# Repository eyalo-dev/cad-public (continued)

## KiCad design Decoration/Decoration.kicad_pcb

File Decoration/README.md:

Name:
- Decoration

Description:
- Decoration/fun, ball shap (christmas ornament), blinking LEDs.

Source refrence:
- Elektor Electronics 1003-12 p.104

This is functional similar but not exact copy.
All dimensions were estimated by eye.
Tried to use similar component placment as much as posible, but using only Kicad
standard PCB component footprint library, so dimentions may very.

PCB
- Done edit but
- Not tested

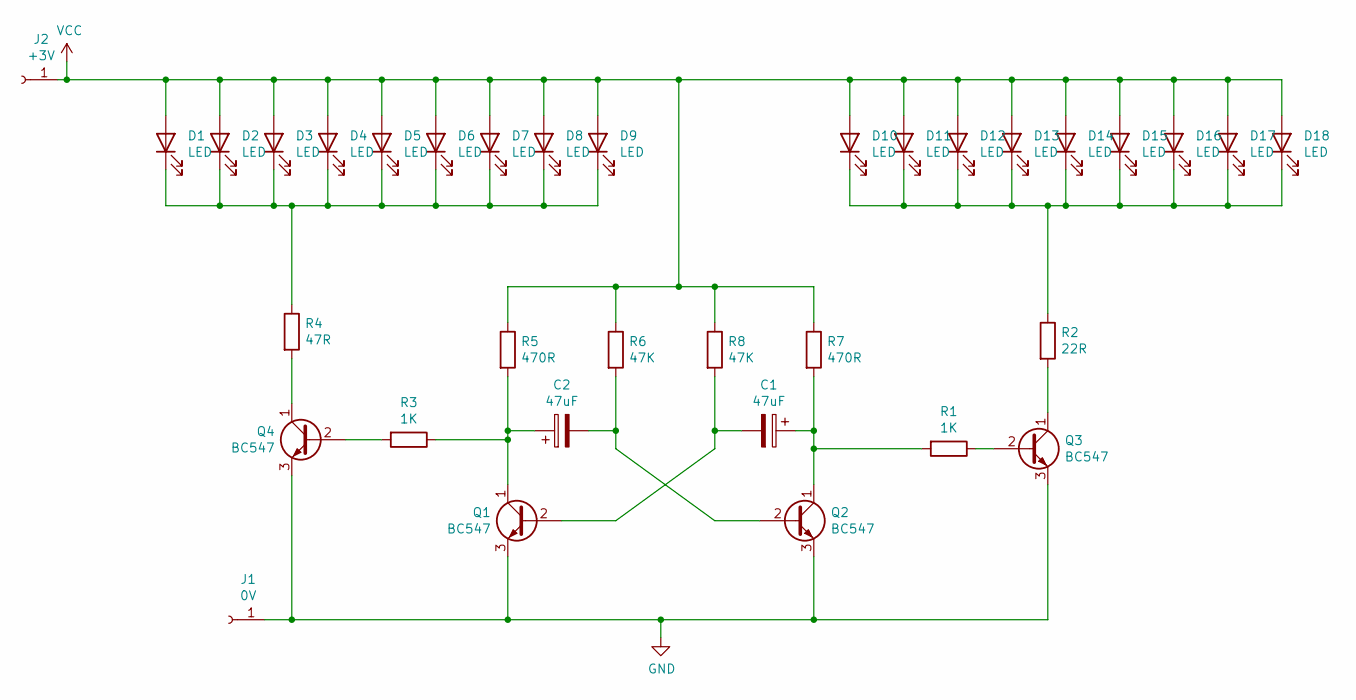
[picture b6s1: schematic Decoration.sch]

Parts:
C1, C2: 47uF; CP_Radial_Tantal_D7.0mm_P5.00mm
D1, D2, D3, D4, D5, D6, D7, D8, D9, D10, D11, D12, D13, D14, D15, D16, D17, D18: LED; LED_D5.0mm_Clear
J1: 0V; PinHeader_1x01_P2.54mm_Vertical
J2: +3V; PinHeader_1x01_P2.54mm_Vertical
Q1, Q2, Q3, Q4: BC547; TO-92_Inline
R1, R3: 1K; R_Axial_DIN0207_L6.3mm_D2.5mm_P10.16mm_Horizontal
R2: 22R; R_Axial_DIN0207_L6.3mm_D2.5mm_P10.16mm_Horizontal
R4: 47R; R_Axial_DIN0207_L6.3mm_D2.5mm_P10.16mm_Horizontal
R5, R7: 470R; R_Axial_DIN0207_L6.3mm_D2.5mm_P10.16mm_Horizontal
R6, R8: 47K; R_Axial_DIN0207_L6.3mm_D2.5mm_P10.16mm_Horizontal

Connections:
GND: J1.1, Q1.3 (E), Q2.3 (E), Q3.3 (E), Q4.3 (E)
unnamed: C1.1, Q2.1 (C), R1.2, R7.2
unnamed: C1.2, Q1.2 (B), R8.2
unnamed: C2.1, Q1.1 (C), R3.1, R5.2
unnamed: C2.2, Q2.2 (B), R6.2
unnamed: D1.1 (K), D2.1 (K), D3.1 (K), D4.1 (K), D5.1 (K), D6.1 (K), D7.1 (K), D8.1 (K), D9.1 (K), R4.1
unnamed: D10.1 (K), D11.1 (K), D12.1 (K), D13.1 (K), D14.1 (K), D15.1 (K), D16.1 (K), D17.1 (K), D18.1 (K), R2.1
unnamed: Q3.1 (C), R2.2
unnamed: Q3.2 (B), R1.1
unnamed: Q4.1 (C), R4.2
unnamed: Q4.2 (B), R3.2
VCC: D1.2 (A), D2.2 (A), D3.2 (A), D4.2 (A), D5.2 (A), D6.2 (A), D7.2 (A), D8.2 (A), D9.2 (A), D10.2 (A), D11.2 (A), D12.2 (A), D13.2 (A), D14.2 (A), D15.2 (A), D16.2 (A), D17.2 (A), D18.2 (A), J2.1, R5.1, R6.1, R7.1, R8.1

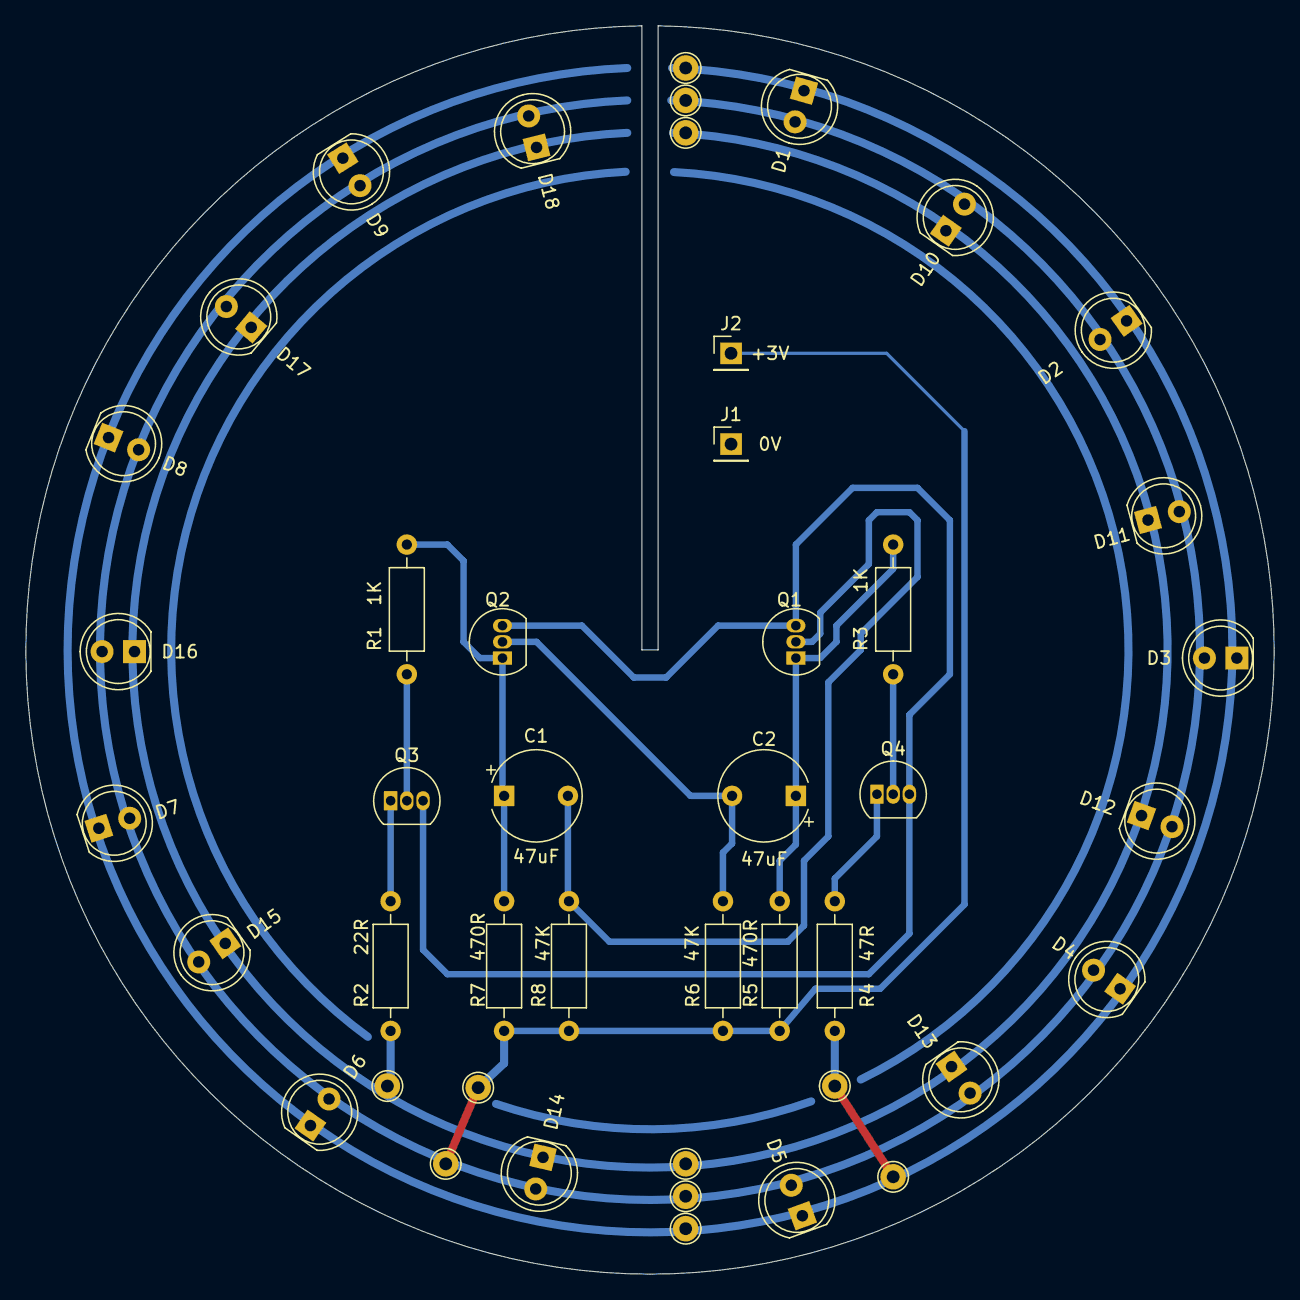
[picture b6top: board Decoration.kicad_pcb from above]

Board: 2 copper layers, 97.8 x 97.8 mm, 34 parts (0 on the bottom side), 12 nets.

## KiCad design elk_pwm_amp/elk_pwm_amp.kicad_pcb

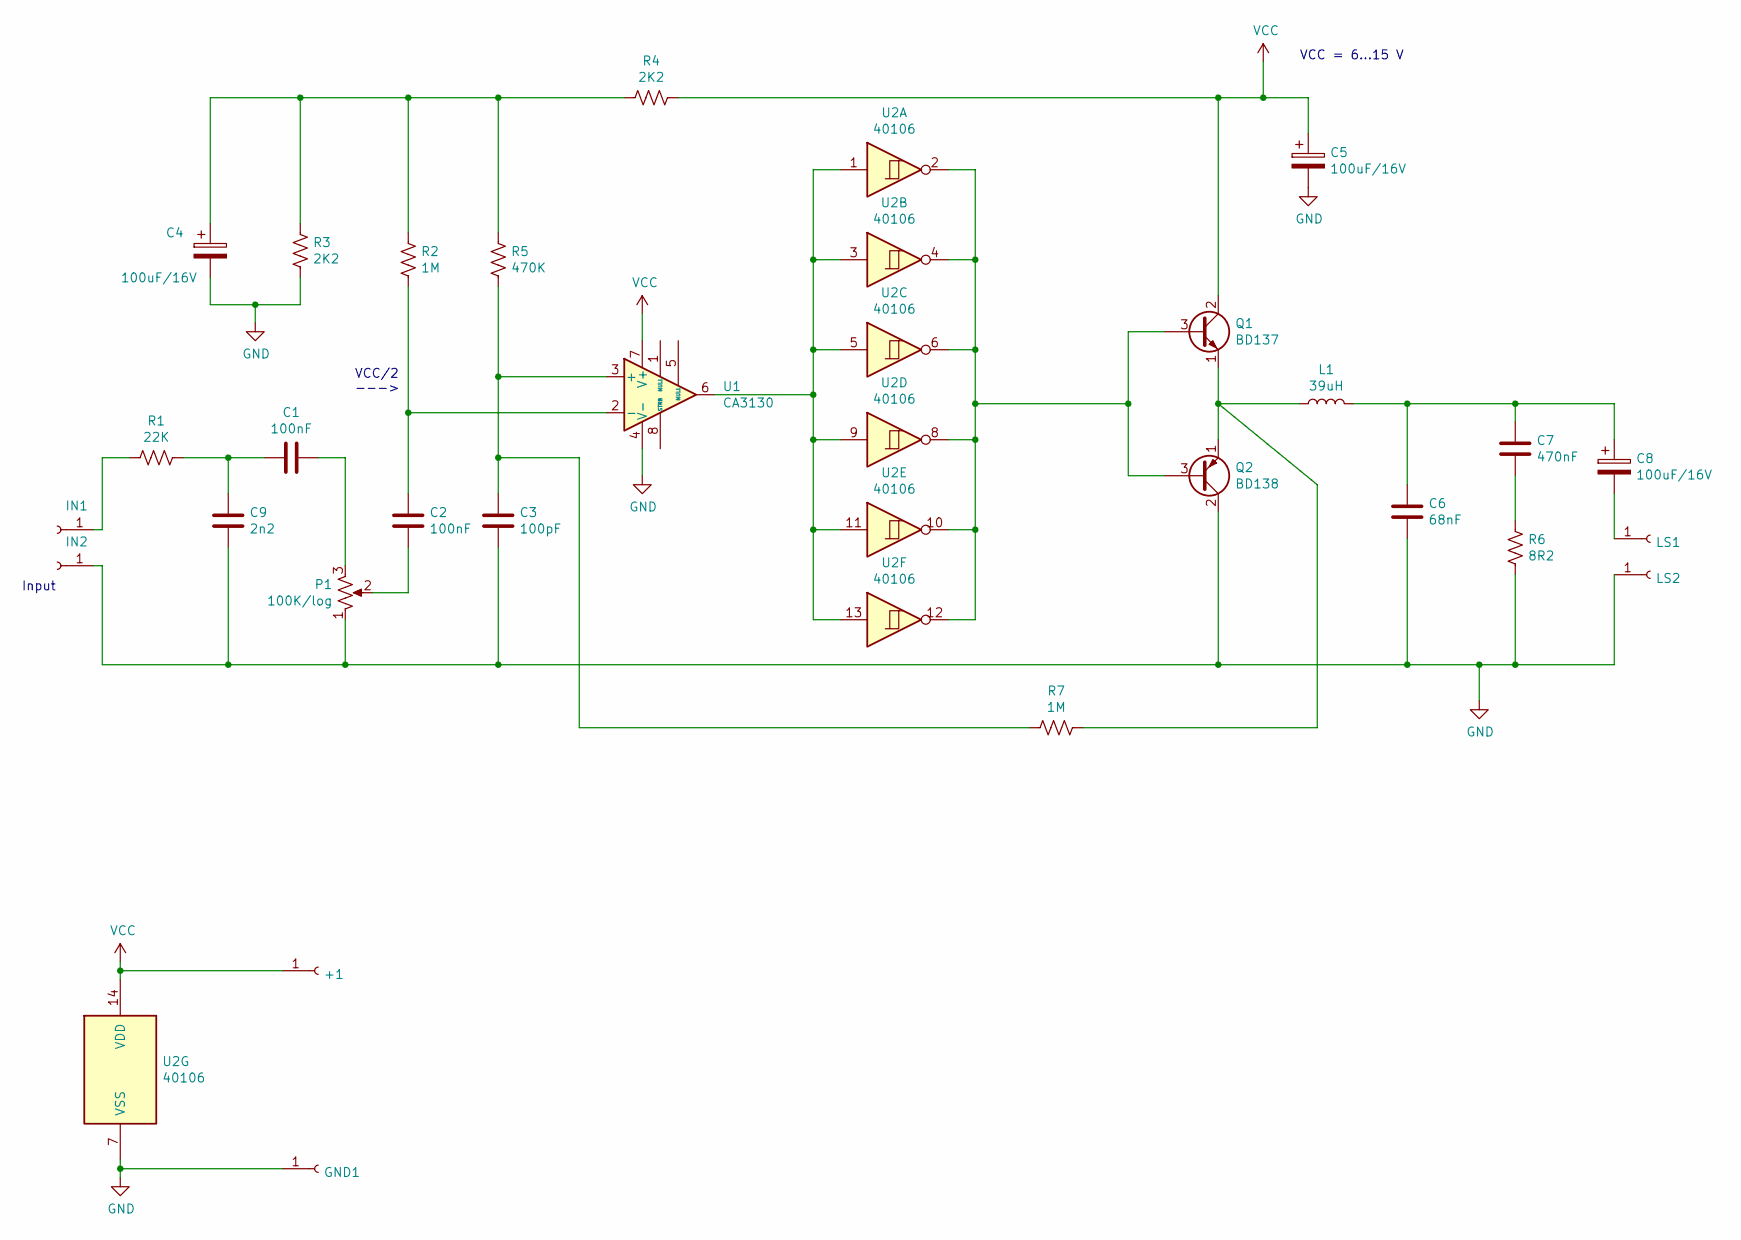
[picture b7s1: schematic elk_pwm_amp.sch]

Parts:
+1: PinHeader_1x01_P2.54mm_Vertical
C1, C2: 100nF; C_Disc_D5.0mm_W2.5mm_P5.00mm
C3: 100pF; C_Disc_D5.0mm_W2.5mm_P5.00mm
C4, C5: 100uF/16V; CP_Axial_L11.0mm_D6.0mm_P18.00mm_Horizontal
C6: 68nF; C_Disc_D5.0mm_W2.5mm_P5.00mm
C7: 470nF; C_Disc_D5.0mm_W2.5mm_P5.00mm
C8: 100uF/16V; CP_Axial_L21.0mm_D8.0mm_P28.00mm_Horizontal
C9: 2n2; C_Disc_D5.0mm_W2.5mm_P5.00mm
GND1: PinHeader_1x01_P2.54mm_Vertical
IN1, IN2: PinHeader_1x01_P2.54mm_Vertical
L1: 39uH; C_Disc_D5.0mm_W2.5mm_P5.00mm
LS1, LS2: PinHeader_1x01_P2.54mm_Vertical
P1: 100K/log; Potentiometer_Alps_RK163_Single_Horizontal
Q1: BD137; TO-126-3_Vertical
Q2: BD138; TO-126-3_Vertical
R1: 22K; R_Axial_DIN0309_L9.0mm_D3.2mm_P12.70mm_Horizontal
R2, R7: 1M; R_Axial_DIN0309_L9.0mm_D3.2mm_P12.70mm_Horizontal
R3, R4: 2K2; R_Axial_DIN0309_L9.0mm_D3.2mm_P12.70mm_Horizontal
R5: 470K; R_Axial_DIN0309_L9.0mm_D3.2mm_P12.70mm_Horizontal
R6: 8R2; R_Axial_DIN0309_L9.0mm_D3.2mm_P12.70mm_Horizontal
U1: CA3130; DIP-8_W7.62mm_Socket_LongPads
U2: 40106; DIP-14_W7.62mm_Socket_LongPads

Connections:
GND: C3.2, C4.2, C5.2, C6.2, C9.2, GND1.1, IN2.1, LS2.1, P1.1, Q2.2 (C), R3.2, R6.2, U1.4 (V-), U2.7 (VSS)
unnamed: C1.1, P1.3
unnamed: C1.2, C9.1, R1.1
unnamed: C2.1, R2.2, U1.2 (-)
unnamed: C2.2, P1.2
unnamed: C3.1, R5.2, R7.2, U1.3 (+)
unnamed: C4.1, R2.1, R3.1, R4.2, R5.1
unnamed: C6.1, C7.1, C8.1, L1.2
unnamed: C7.2, R6.1
unnamed: C8.2, LS1.1
unnamed: IN1.1, R1.2
unnamed: L1.1, Q1.1 (E), Q2.1 (E), R7.1
unnamed: Q1.3 (B), Q2.3 (B), U2.2, U2.4, U2.6, U2.8, U2.10, U2.12
unnamed: U1.6, U2.1, U2.3, U2.5, U2.9, U2.11, U2.13
VCC: +1.1, C5.1, Q1.2 (C), R4.1, U1.7 (V+), U2.14 (VDD)

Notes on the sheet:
Input
VCC = 6...15 V
VCC/2 --->

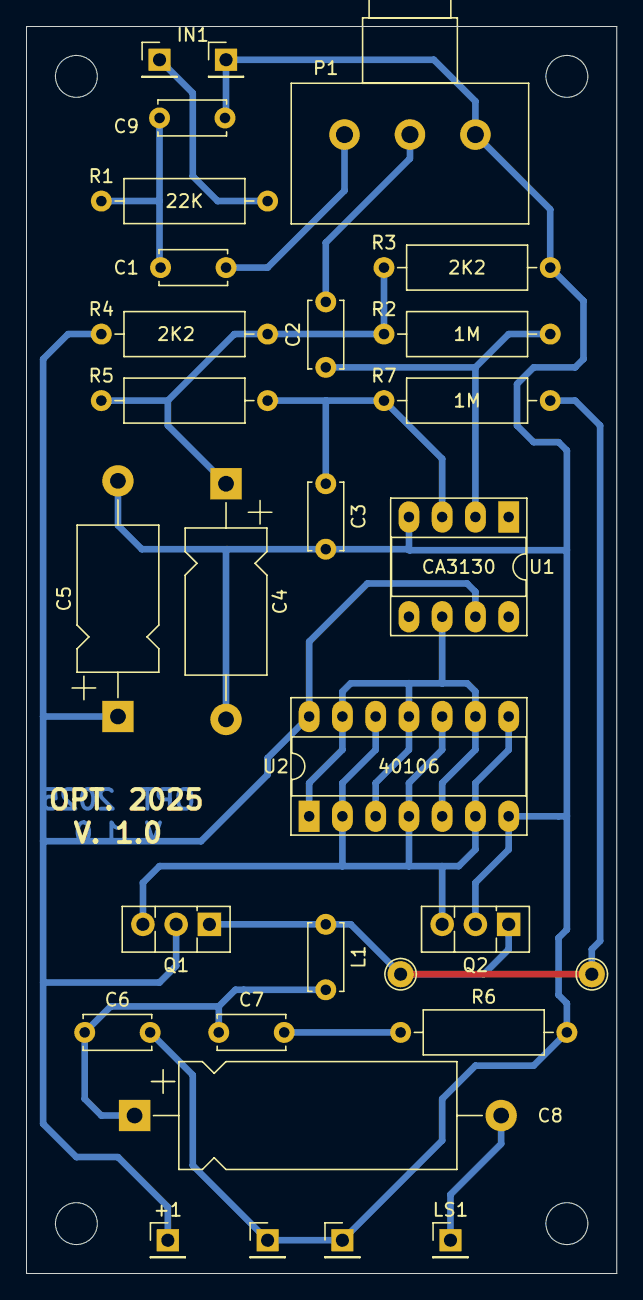
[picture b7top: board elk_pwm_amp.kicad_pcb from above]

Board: 2 copper layers, 45.1 x 95.2 mm, 28 parts (0 on the bottom side), 15 nets.

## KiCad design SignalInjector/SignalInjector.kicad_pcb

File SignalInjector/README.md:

Name:
- SignalInjector

Description:
- Battery (4*1.5V) operated analog signal injector.

Source reference:
- Elektor May 1984 (Elektor_1984-05.pdf) page 54.
- Elektor 301 circuits vol1, p. 71 (#58).
- No (Elektor) PCB number.

This is functional similar but not exact copy.
All dimension were estimated by eye.
Tried to use similar component placment as much as posible, but using only Kicad
standard PCB component footprint library, so dimentions may very.

PCB
- Done edit but
- Not tested

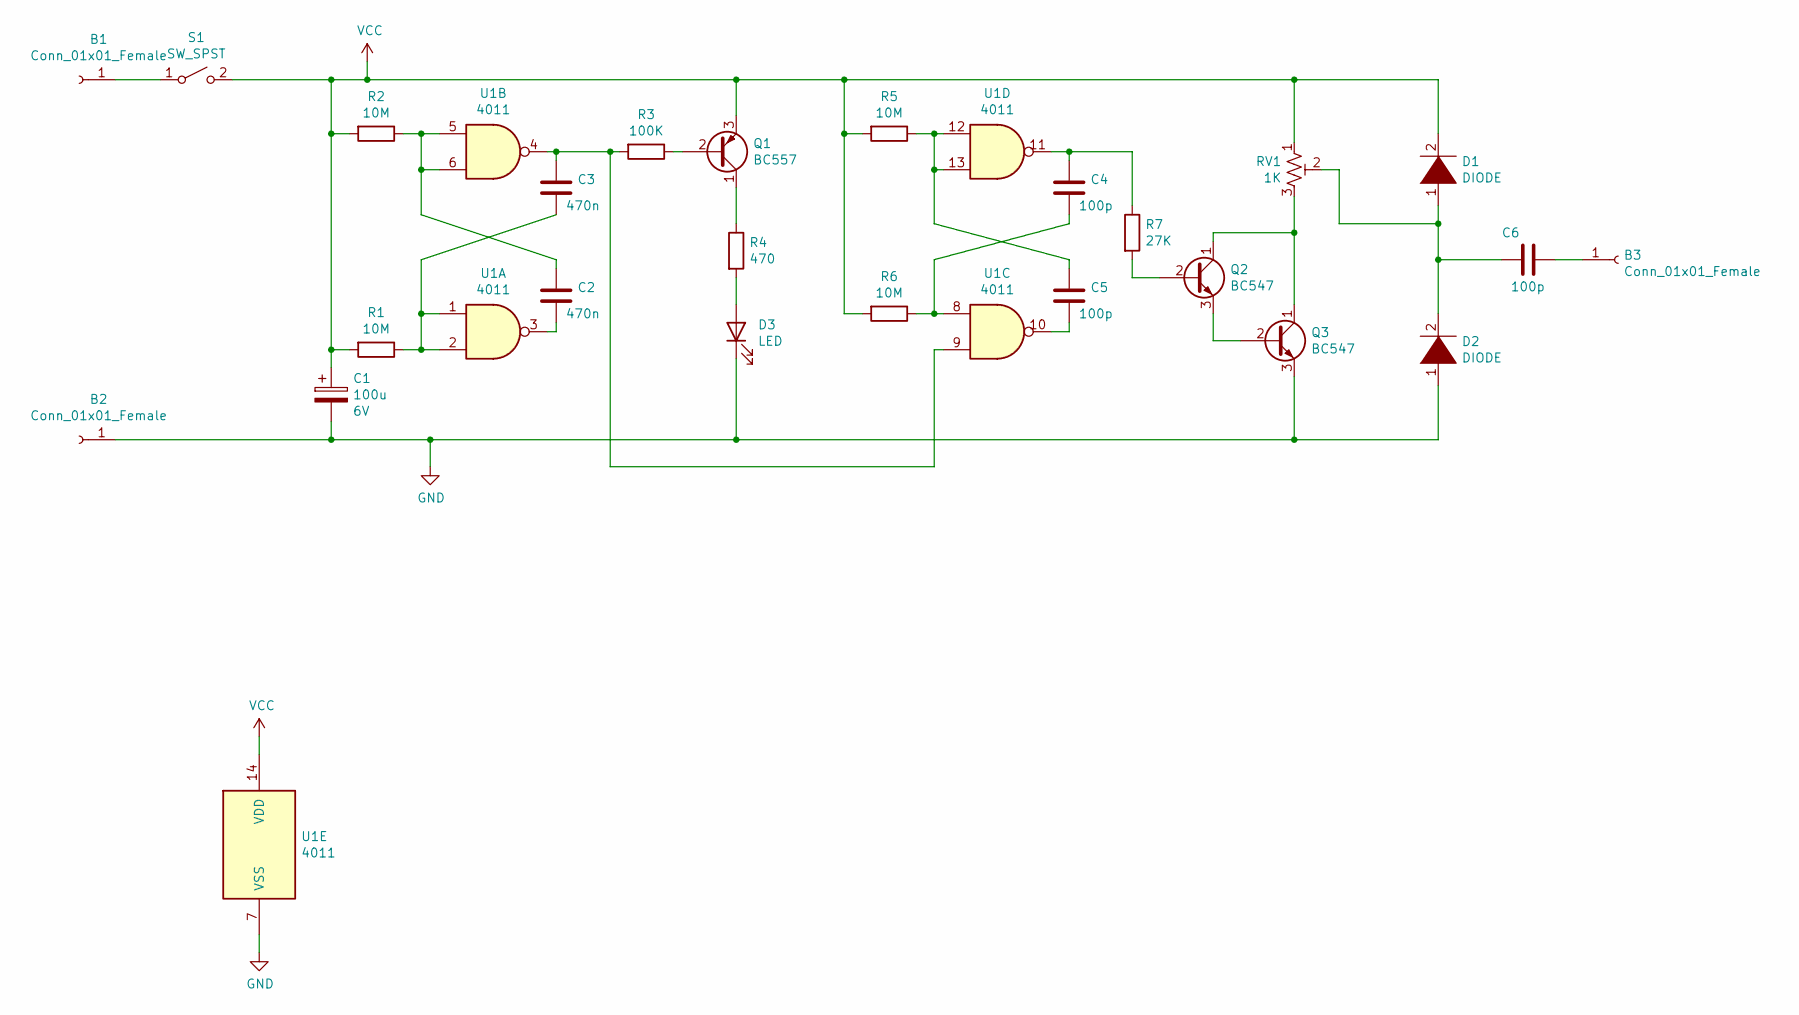
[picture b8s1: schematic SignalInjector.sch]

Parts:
B1, B2, B3: Conn_01x01_Female; Pin_D1.0mm_L10.0mm
C1: 100u; CP_Radial_Tantal_D7.0mm_P5.00mm
C2, C3: 470n; C_Axial_L5.1mm_D3.1mm_P7.50mm_Horizontal
C4, C5: 100p; C_Axial_L5.1mm_D3.1mm_P7.50mm_Horizontal
C6: 100p; C_Axial_L5.1mm_D3.1mm_P10.00mm_Horizontal
D1, D2: DIODE; D_A-405_P7.62mm_Horizontal
D3: LED; LED_D5.0mm_FlatTop
Q1: BC557; TO-92
Q2, Q3: BC547; TO-92
R1, R2, R5, R6: 10M; R_Axial_DIN0207_L6.3mm_D2.5mm_P10.16mm_Horizontal
R3: 100K; R_Axial_DIN0207_L6.3mm_D2.5mm_P10.16mm_Horizontal
R4: 470; R_Axial_DIN0207_L6.3mm_D2.5mm_P10.16mm_Horizontal
R7: 27K; R_Axial_DIN0207_L6.3mm_D2.5mm_P10.16mm_Horizontal
RV1: 1K; Potentiometer_ACP_CA6-H2,5_Horizontal
S1: SW_SPST; SW_CW_GPTS203211B
U1: 4011; DIP-14_W7.62mm_Socket_LongPads

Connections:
GND: B2.1, C1.2, D2.1 (K), D3.1 (K), Q3.3 (E), U1.7 (VSS)
unnamed: B1.1, S1.1 (A)
unnamed: B3.1, C6.1
unnamed: C2.1, R2.1, U1.5, U1.6
unnamed: C2.2, U1.3
unnamed: C3.1, R3.2, U1.4, U1.9
unnamed: C3.2, R1.1, U1.1, U1.2
unnamed: C4.1, R7.1, U1.11
unnamed: C4.2, R6.1, U1.8
unnamed: C5.1, R5.1, U1.12, U1.13
unnamed: C5.2, U1.10
unnamed: C6.2, D1.1 (K), D2.2 (A), RV1.2
unnamed: D3.2 (A), R4.2
unnamed: Q1.1 (C), R4.1
unnamed: Q1.2 (B), R3.1
unnamed: Q2.1 (C), Q3.1 (C), RV1.3
unnamed: Q2.2 (B), R7.2
unnamed: Q2.3 (E), Q3.2 (B)
VCC: C1.1, D1.2 (A), Q1.3 (E), R1.2, R2.2, R5.2, R6.2, RV1.1, S1.2 (B), U1.14 (VDD)

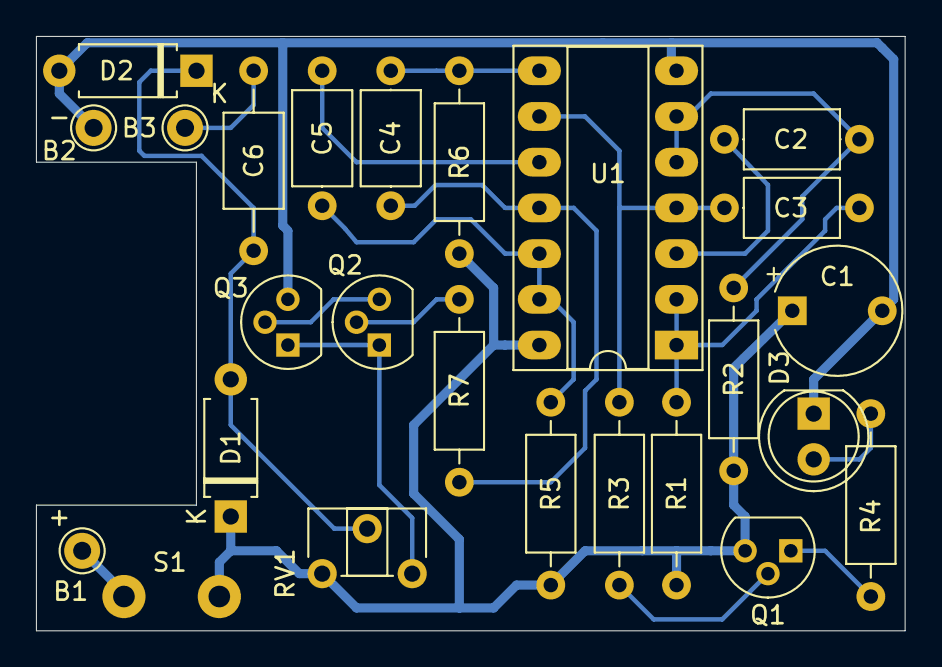
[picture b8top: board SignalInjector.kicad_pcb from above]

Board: 2 copper layers, 48.3 x 33.0 mm, 25 parts (1 on the bottom side), 19 nets.

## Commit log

2025-12-29 update comments
2025-12-29 more files for initial commit
2025-12-29 more of the initial commit files
2025-12-31 update docs
2026-05-05 update readme.md files
2026-05-05 add Decoration PCB
2026-05-24 add Proto_no2 and SoundGen PCBs
2026-05-24 add SmoothOperator
2026-05-24 update ETI-438, make PCB smaller
2026-06-13 add PIC small pic count demo board
2026-06-13 fix typo errors
